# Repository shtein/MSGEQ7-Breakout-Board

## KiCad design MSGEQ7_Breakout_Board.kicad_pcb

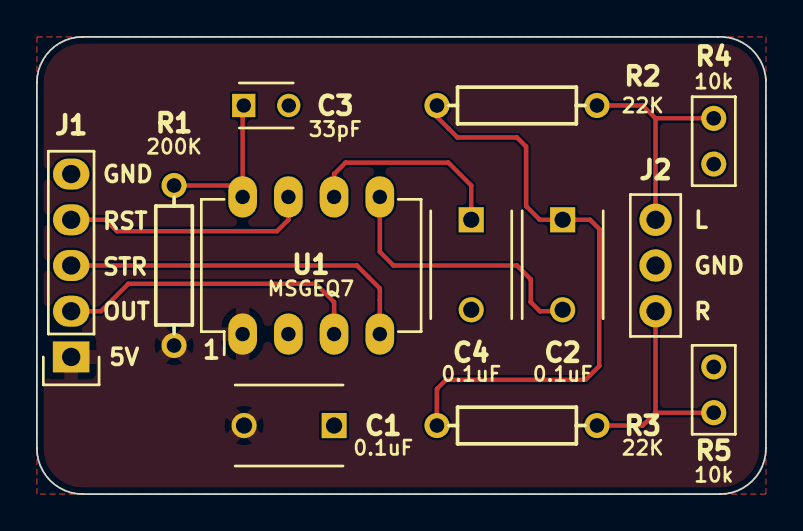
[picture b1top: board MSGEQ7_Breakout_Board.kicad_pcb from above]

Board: 2 copper layers, 40.5 x 25.4 mm, 12 parts (0 on the bottom side), 11 nets.

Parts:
C1, C2, C4: 0.1uF; C_Disc_D6_P5
C3: 33pF; C_Disc_D3_P2.5
J1: BREAKOUT_BOARD_HEADER; Pin_Header_Straight_1x05
J2: AUDIO_IN_HEADER; PinHeader_1x03_P2.54mm_Vertical
R1: 200K; PTH_Resistor
R2, R3: 22K; PTH_Resistor
R4, R5: 10k; R_Axial_DIN0207_L6.3mm_D2.5mm_P2.54mm_Vertical
U1: MSGEQ7; DIP-8_W7.62mm_LongPads

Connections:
+5V: C1.2, J1.1, R1.2, U1.1
AUDIO_L: J2.3, R2.2, R4.1
AUDIO_R: J2.1, R3.2, R5.1
GND: C1.1, C3.2, C4.2, J1.5, J2.2, R4.2, R5.2, U1.2
unnamed: C2.1, R2.1, R3.1
unnamed: C2.2, U1.5
unnamed: C3.1, R1.1, U1.8
unnamed: C4.1, U1.6
OUT: J1.2, U1.3
RESET_IN: J1.4, U1.7
STROBE: J1.3, U1.4
